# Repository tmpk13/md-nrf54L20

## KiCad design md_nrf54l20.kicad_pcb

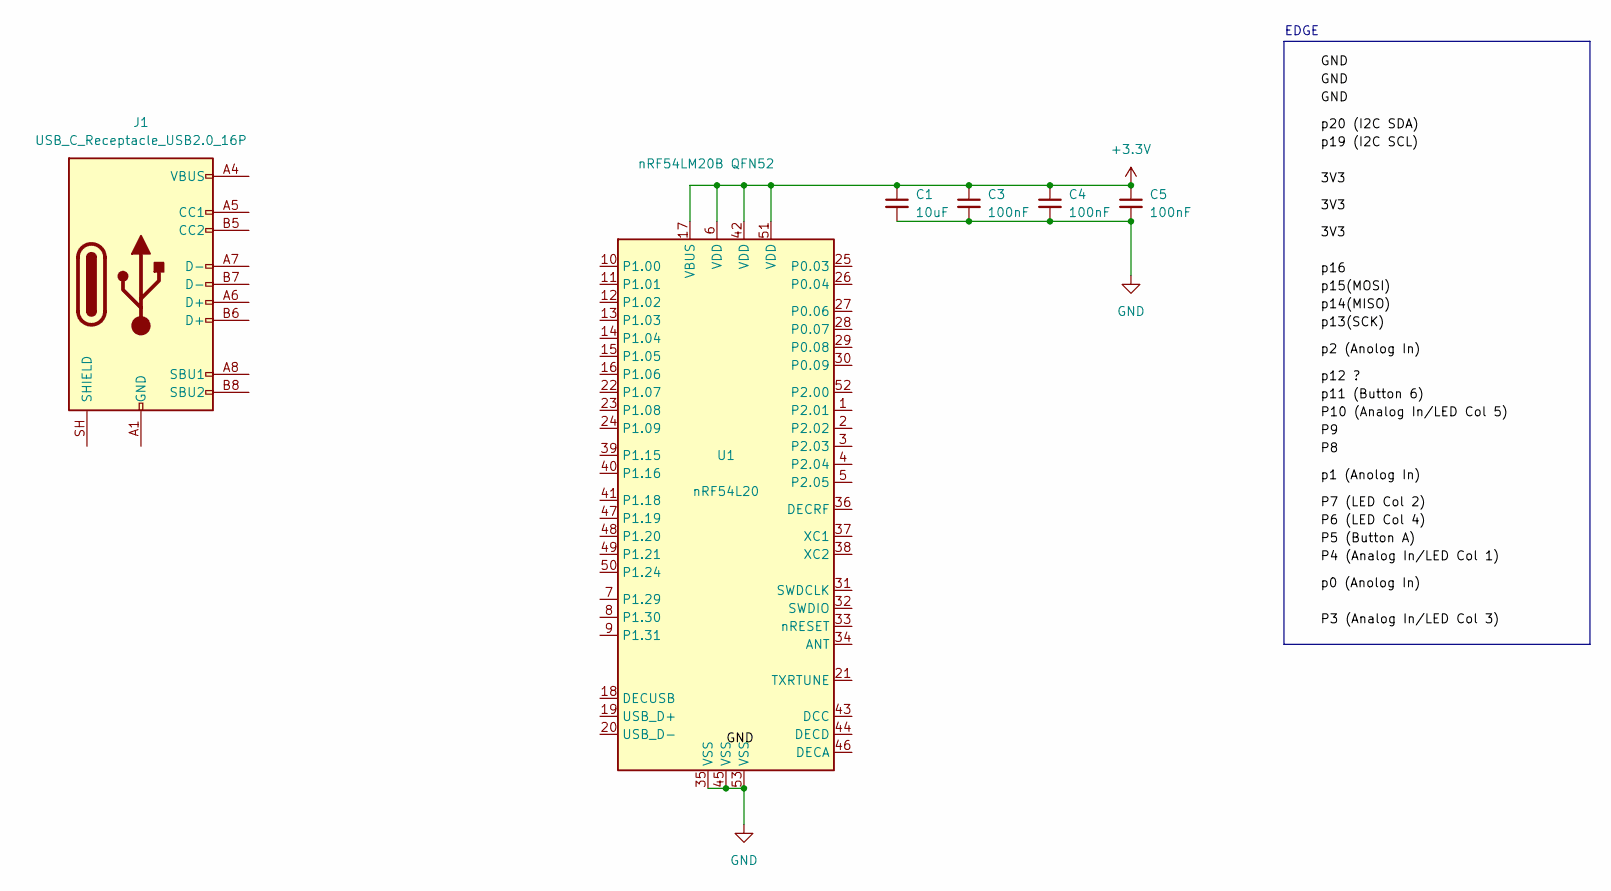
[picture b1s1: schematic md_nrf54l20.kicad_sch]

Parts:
C1: 10uF; C_0201_0603Metric
C3, C4, C5: 100nF; C_0201_0603Metric
J1: USB_C_Receptacle_USB2.0_16P; USB_C_Receptacle_G-Switch_GT-USB-7010ASV
U1: nRF54L20; QFN-52-1EP_6x6mm_P0.4mm_EP4.7x4.7mm

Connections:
GND: C1.2, C3.2, C4.2, C5.2, U1.35 (VSS), U1.45 (VSS), U1.53 (VSS)
unnamed: J1.A1 (GND), J1.A12 (GND), J1.B1 (GND), J1.B12 (GND)
unnamed: J1.A4 (VBUS), J1.A9 (VBUS), J1.B4 (VBUS), J1.B9 (VBUS)
unnamed: C1.1, C3.1, C4.1, C5.1, U1.6 (VDD), U1.17 (VBUS), U1.42 (VDD), U1.51 (VDD)

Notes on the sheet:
EDGE

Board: 2 copper layers, 6 parts (0 on the bottom side), 4 nets, no tracks yet.

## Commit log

2026-06-07 Update symbols
2026-06-12 Update layout
